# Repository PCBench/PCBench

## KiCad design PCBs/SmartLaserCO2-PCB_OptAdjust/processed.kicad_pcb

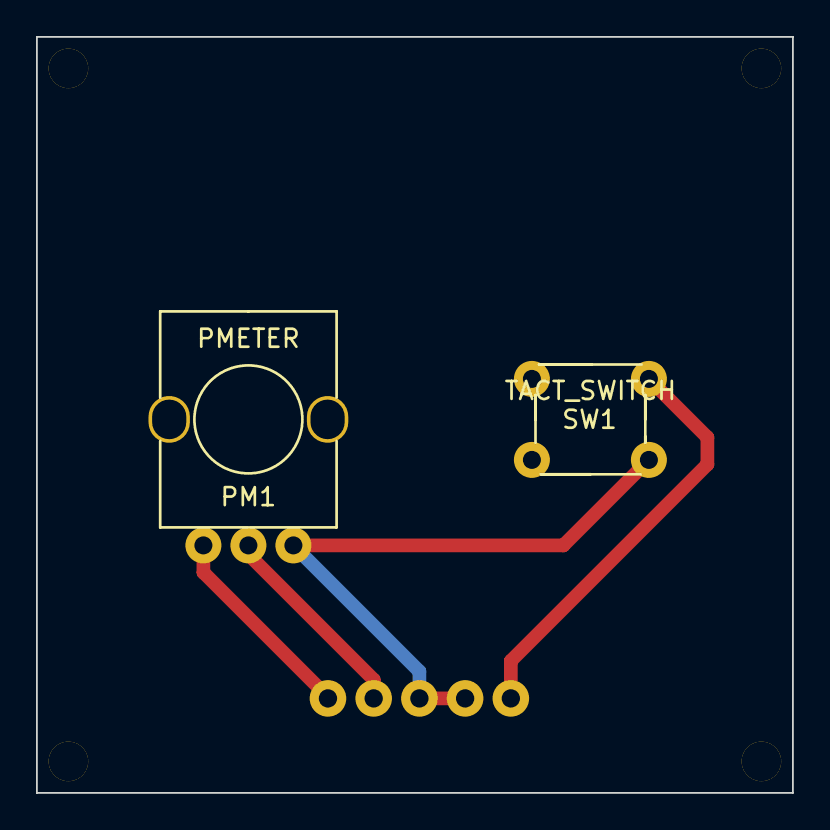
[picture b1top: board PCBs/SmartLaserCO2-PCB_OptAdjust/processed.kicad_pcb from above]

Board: 2 copper layers, 42.0 x 42.0 mm, 7 parts (1 on the bottom side), 4 nets.

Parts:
J1: CONN_5; S5B-XH-A
PM1: PMETER; WH09A-2
Ref**: Val**; HOLE_M2
Ref**_2, Ref**_3, Ref**_4: Val**; HOLE_M2
SW1: TACT_SWITCH; TSA06131

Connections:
GND: J1.3, J1.4, PM1.3, SW1.2
unnamed: J1.1, PM1.1
unnamed: J1.2, PM1.2
unnamed: J1.5, SW1.1

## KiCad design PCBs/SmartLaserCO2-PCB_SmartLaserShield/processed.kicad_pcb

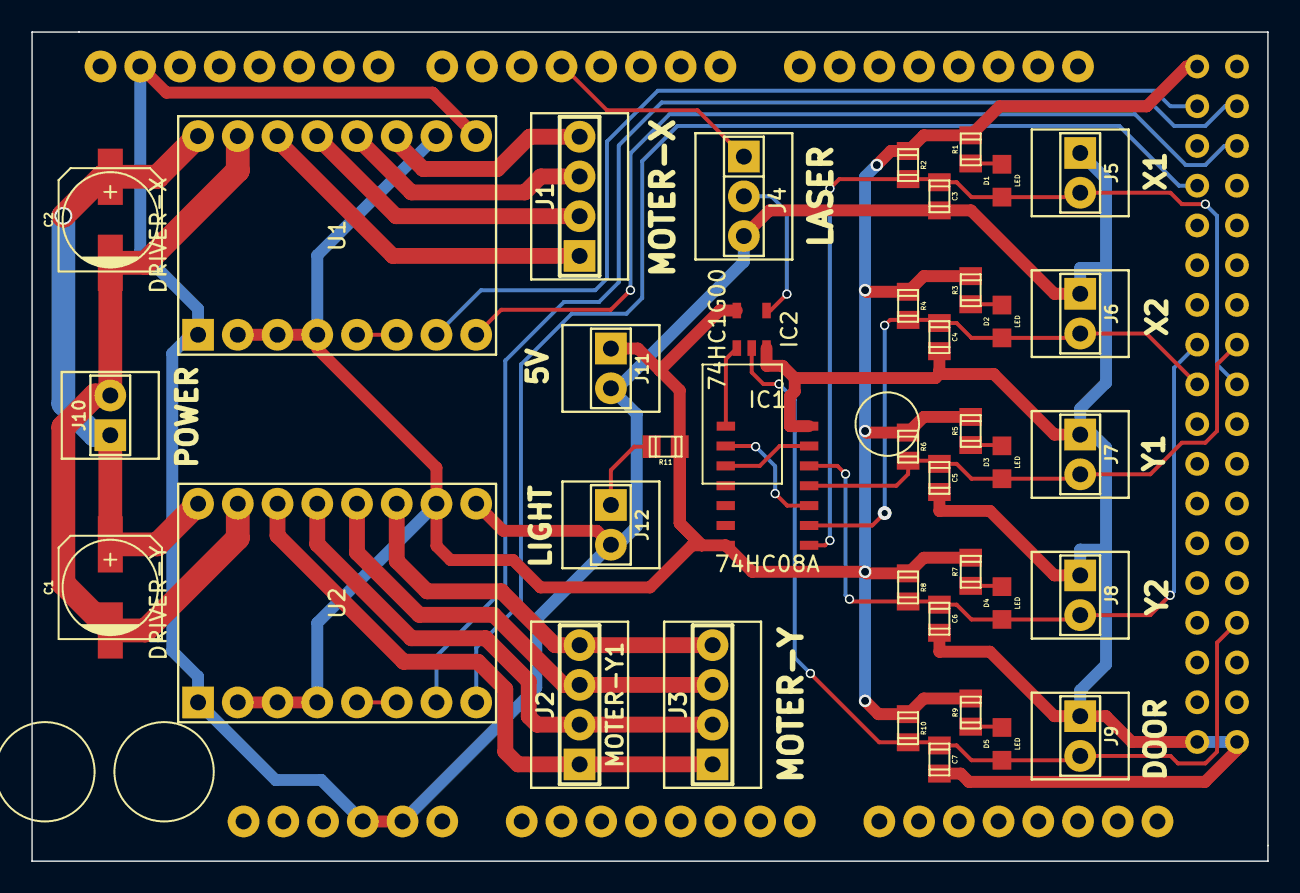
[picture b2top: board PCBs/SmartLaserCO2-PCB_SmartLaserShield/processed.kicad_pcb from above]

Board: 2 copper layers, 79.0 x 53.0 mm, 40 parts (0 on the bottom side), 34 nets.

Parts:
C1, C2: 100uF; C_ELEC_6.3x7.7
C3, C4, C5, C6, C7: 0u1; C_0805
D1, D2, D3, D4, D5: LED; C_LED
IC1: 74HC08A
IC2: 74HC1G00
J1: MOTER-X; PIN_ARRAY_4x1
J2: MOTER-Y1; PIN_ARRAY_4x1
J3: MOTER-Y; PIN_ARRAY_4x1
J4: LASER; PIN_ARRAY_3X1
J5: X1; PIN_ARRAY_2X1
J6: X2; PIN_ARRAY_2X1
J7: Y1; PIN_ARRAY_2X1
J8: Y2; PIN_ARRAY_2X1
J9: DOOR; PIN_ARRAY_2X1
J10: POWER; PIN_ARRAY_2X1
J11: 5V; PIN_ARRAY_2X1
J12: LIGHT; PIN_ARRAY_2X1
R1, R3, R5, R7, R9: 1K; C_0805
R2, R4, R6, R8, R10: 10K; C_0805
R11: 150; C_0805
U1: DRIVER-X; A4988
U2: DRIVER-Y; A4988
U3: ARDUINO_MEGA

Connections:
GND: C3.1, C4.1, C5.1, C6.1, C7.1, IC1.7, IC2.3, J4.3, J5.1, J6.1, J7.1, J8.1, J9.1, J11.2, J12.2, U1.1, U1.9, U2.1, U2.9, U3.GND1, U3.GND2, U3.GND3, U3.GND4, U3.GND5
unnamed: J1.2, U1.13
unnamed: J1.3, U1.12
unnamed: J1.4, U1.11
unnamed: J1.1, U1.14
unnamed: IC1.8, IC2.1
unnamed: J2.3, J3.3, U2.12
unnamed: J2.1, J3.1, U2.14
unnamed: J2.2, J3.2, U2.13
unnamed: J2.4, J3.4, U2.11
unnamed: U1.5, U1.6
unnamed: U2.5, U2.6
unnamed: IC1.3, IC1.9
unnamed: IC1.6, IC1.10
unnamed: J4.1, U3.4
unnamed: U1.7, U3.22
unnamed: U2.7, U3.23
unnamed: IC2.4, J4.2
unnamed: J12.1, R11.1
unnamed: U1.8, U3.25
unnamed: U2.8, U3.26
unnamed: D3.1, R5.2
unnamed: D1.1, R1.2
unnamed: C3.2, D1.2, IC1.1, J5.2, R2.1, U3.37
unnamed: D2.1, R3.2
unnamed: C4.2, D2.2, IC1.2, J6.2, R4.1, U3.36
unnamed: C6.2, D4.2, IC1.5, J8.2, R8.1, U3.34
unnamed: D5.1, R9.2
unnamed: C7.2, D5.2, IC2.2, J9.2, R10.1, U3.49
unnamed: C5.2, D3.2, IC1.4, J7.2, R6.1, U3.35
unnamed: D4.1, R7.2
unnamed: C1.1, C2.1, J10.1, U1.16, U2.16
unnamed: C1.2, C2.2, J10.2, U1.15, U2.15
VDD: IC1.14, IC2.5, J11.1, R1.1, R2.2, R3.1, R4.2, R5.1, R6.2, R7.1, R8.2, R9.1, R10.2, R11.2, U1.2, U1.3, U1.4, U1.10, U2.2, U2.3, U2.4, U2.10, U3.5V_4

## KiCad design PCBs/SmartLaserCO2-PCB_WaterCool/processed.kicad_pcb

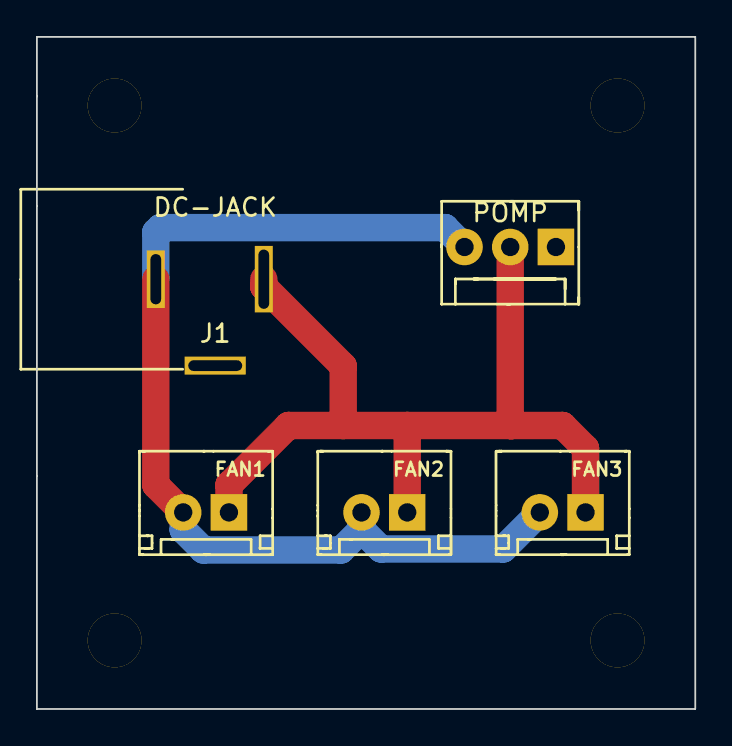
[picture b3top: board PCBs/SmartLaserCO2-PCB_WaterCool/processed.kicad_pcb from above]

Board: 2 copper layers, 36.6 x 37.3 mm, 9 parts (0 on the bottom side), 2 nets.

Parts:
J1: DC-JACK; DC-005
J2: POMP; 640454-3
J3: FAN1; B2B-XH-A
J4: FAN2; B2B-XH-A
J5: FAN3; B2B-XH-A
Ref**: Val**; HOLE_M3
Ref**_2, Ref**_3, Ref**_4: Val**; HOLE_M3

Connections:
+12V: J1.1, J2.2, J3.1, J4.1, J5.1
GND: J1.2, J2.3, J3.2, J4.2, J5.2

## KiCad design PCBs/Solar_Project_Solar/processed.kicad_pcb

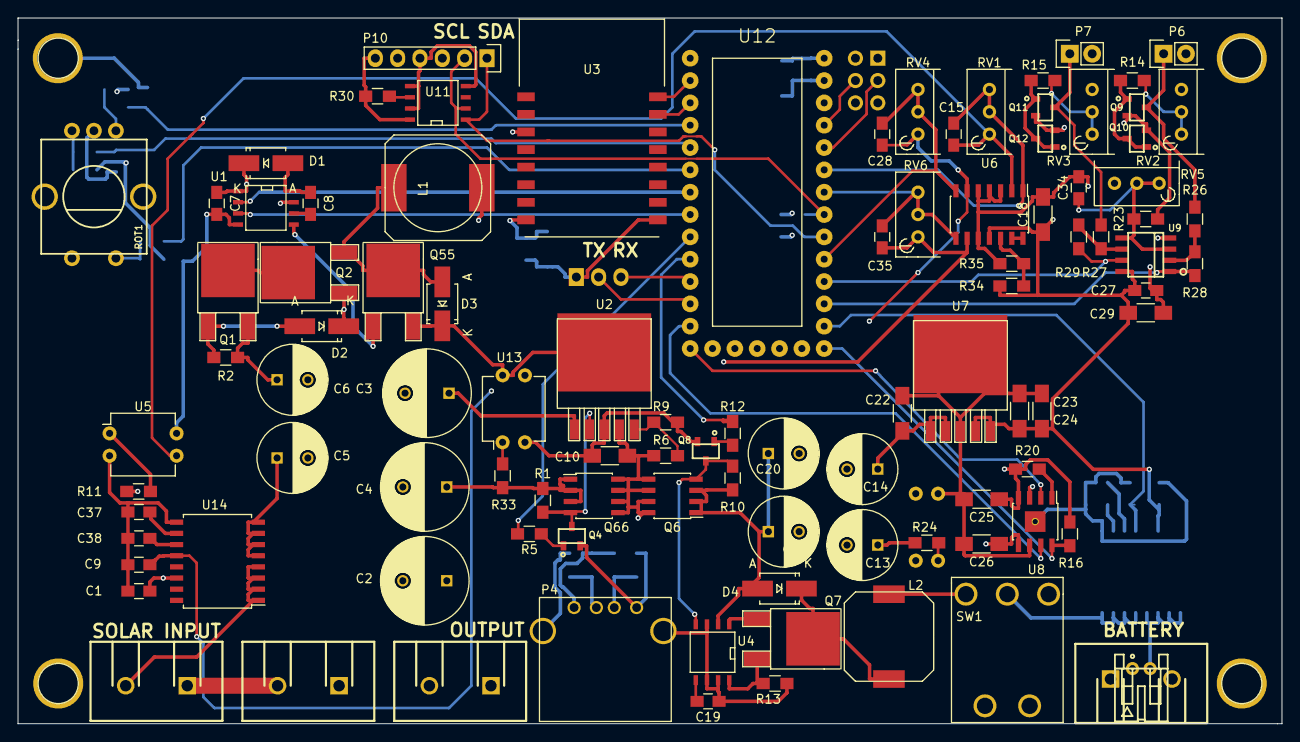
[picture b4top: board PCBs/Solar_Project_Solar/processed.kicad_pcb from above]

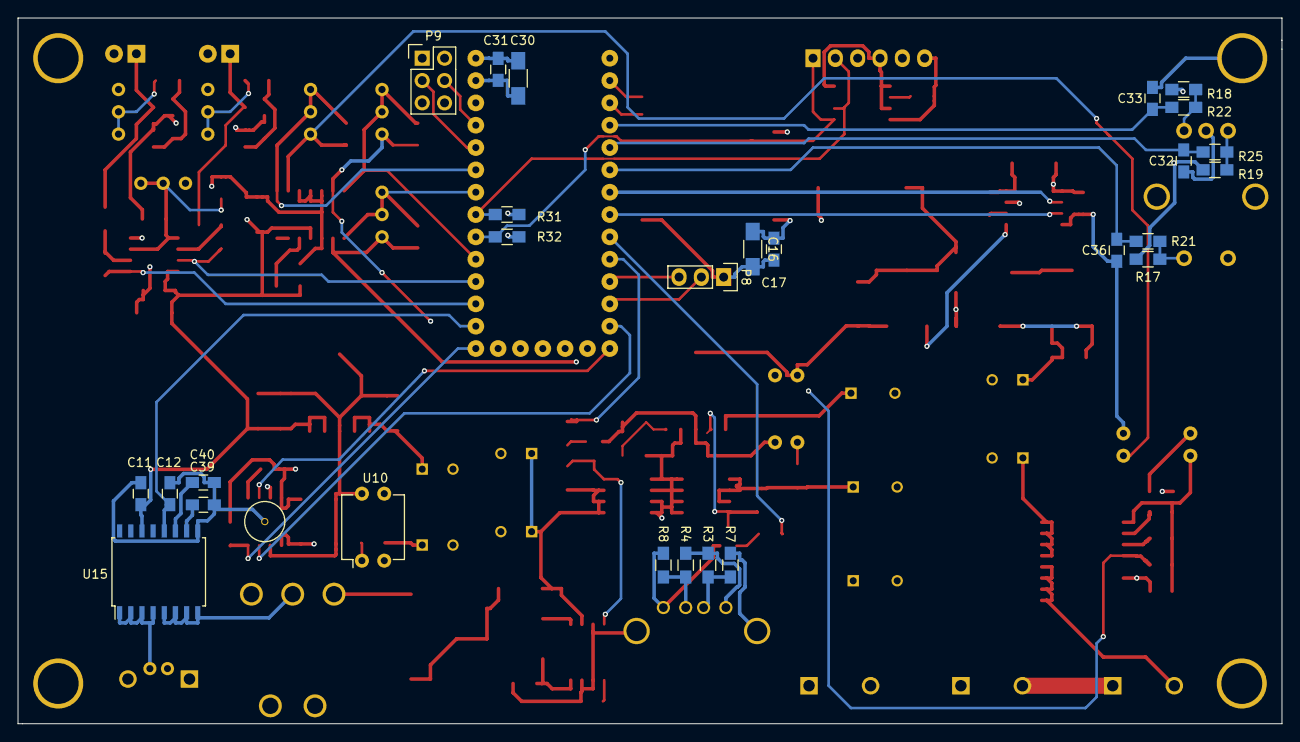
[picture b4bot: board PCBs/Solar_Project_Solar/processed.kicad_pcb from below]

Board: 4 copper layers, 143.8 x 80.3 mm, 127 parts (27 on the bottom side), 80 nets.

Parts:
C1, C7, C8, C9, C11, C12, C17, C19, C27, C31, C37, C38, C39, C40: .1u; C_0805_HandSoldering
C2, C3, C4: 1000u; C_Radial_D10_L16_P5
C5, C6, C13, C14, C20, C21: 220U; C_Radial_D8_L11.5_P3.5
C10, C16, C18, C22, C23, C24, C25, C26, C29, C30: 22U; C_1206_HandSoldering
C15, C28, C32, C33, C35, C36: .01u; C_0805_HandSoldering
C34: 1u; C_0805_HandSoldering
D1, D2, D3, D4: MBRA340T3G; Diode-SMA_Handsoldering
JST-S2B-PH-K_right-angle-jack: VAL**; JST-S2B-PH-K_right-angle-jack
L1: 330uH; SELF-WE-PD-XXL
L2: 22U; self_cms_we-tpc_XL
P1, P2, P3, P5: CONN_01X02; 1x2-SCREW-TERM_P7.5mm
P4: USB_A
P6, P7: CONN_01X02; Pin_Header_Straight_1x02
P8: CONN_01X03; Pin_Header_Straight_1x03
P9: CONN_02X03; Pin_Header_Straight_2x03
P10: CONN_01X06; Pin_Header_Straight_1x06
Q1, Q2, Q7, Q55: IRF3704Z; DPAK-2
Q4, Q8: PN2222A; SOT23
Q6, Q66: FDS4465; SOIC-8_3.9x4.9mm_Pitch1.27mm
Q9, Q10, Q11, Q12: PNP_BEC; SOT23
R1, R10: 330k; R_0805_HandSoldering
R2, R11, R16, R17, R18, R19, R20, R21, R22, R25, R30, R34, R35: 10k; R_0805_HandSoldering
R3: 42.9k; R_0805_HandSoldering
R4: 74.4k; R_0805_HandSoldering
R5, R12: 1k; R_0805_HandSoldering
R6: 180k; R_0805_HandSoldering
R7, R8: 49.3k; R_0805_HandSoldering
R9: 16k; R_0805_HandSoldering
R13: 50m; R_0805_HandSoldering
R14, R15: 2.2k; R_0805_HandSoldering
R23, R24: 2.7k; R_0805_HandSoldering
R26, R27: 12k; R_0805_HandSoldering
R28, R29: 47k; R_0805_HandSoldering
R31, R32: 4.7k; R_0805_HandSoldering
R33: 3.3k; R_0805_HandSoldering
ROT1: ROTARY-ENCODER; SF-ROTARY-ENCODER
RV1, RV4, RV6: POT; Potentiometer_Bourns_3296W_3-8Zoll_Inline_ScrewUp
RV2, RV3, RV5: 1k; Potentiometer_Bourns_3296W_3-8Zoll_Inline_ScrewUp
SW1: SW_SPDT; SPDT_Toggle
U1: IR2104; SOIC-8-N
U2: MCP1827; DPAK-5
U3: ESP8266; ESP8266_ADAFRUIT_SMD
U4: MAX770; SOIC-8-N
U5, U10, U13: LTV-817; DIP-4_W7.62mm
U6: LMV324; SOIC-14_3.9x8.7mm_Pitch1.27mm
U7: LT1963; DPAK-5
U8: MAX1811; SOIC-8-1EP_3.9x4.9mm_Pitch1.27mm
U9: TL072; SOIC8
U11: DS75; SOIC-8-N
U12: Teensy_3.1
U14, U15: ACS710; SOIC-16_7.5x10.3mm_Pitch1.27mm

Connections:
5V_OUT: C10.1, C25.1, P1.1, P4.1, P9.1, P9.2, Q6.5, Q6.6, Q6.7, Q6.8, Q66.5, Q66.6, Q66.7, Q66.8, R3.1, R4.1, R6.1, R16.1, R20.1, U2.4, U8.4
+3V3: C1.1, C11.1, C16.1, C17.1, C18.1, C23.1, C24.1, C27.1, C29.1, C30.1, C31.1, P10.6, Q9.2, Q10.2, Q11.2, Q12.2, R17.1, R18.1, R19.1, R23.1, R30.1, R31.1, R32.1, R34.1, U3.3, U3.8, U6.11, U7.4, U7.5, U9.8, U11.8, U12.26, U14.14, U15.14
BATTERY_I: C12.1, U12.14, U15.12
BATTERY_INPUT: C13.1, C14.1, C22.1, L2.1, R24.1, SW1.2, U7.1, U7.2
BATTERY_INPUT_BUF: C28.2, RV4.2, RV4.3, U6.7, U12.17
CHRG: R16.2, U8.8, U12.13
CHRG_EN: U8.7, U12.11
CHRG_I: U8.2, U12.12
ESP_RX: U3.15, U12.1
ESP_TX: U3.16, U12.0
GND: C1.2, C2.2, C3.2, C4.2, C5.2, C6.2, C7.2, C9.2, C10.2, C11.2, C12.2, C13.2, C14.2, C16.2, C17.2, C18.2, C19.2, C20.2, C21.2, C22.2, C23.2, C24.2, C25.2, C26.2, C27.2, C29.2, C30.2, C31.2, C32.2, C33.2, C34.2, C36.2, C37.2, C38.2, C39.2, C40.2, D3.1, JST-S2B-PH-K_right-angle-jack.1, P1.2, P3.1, P4.4, P4.5, P5.1, P6.2, P7.2, P8.1, P9.5, P9.6, P10.4, Q4.2, Q8.2, Q55.3, R7.2, R8.2, R9.2, R13.2, R35.2, ROT1.3, ROT1.5, RV2.3, RV3.3, RV5.3, U1.4, U2.3, U3.9, U4.3, U4.6, U4.7, U5.2, U5.4, U6.3, U6.4, U6.5, U6.10, U7.3, U8.3, U8.6, U9.4, U10.2, U10.4, U11.4, U11.5, U11.7, U12.25, U12.27, U12.30, U13.2, U13.4, U14.9, U15.9
LIGHT1: R28.2, U9.1, U12.15
LIGHT2: R29.1, U9.7, U12.16
LOAD_SWITCH: R12.1, U12.8
MPPT_PWM: U1.2, U12.5
unnamed: C5.1, C6.1, C7.1, D1.1, Q1.3, R2.1, U1.1, U14.5, U14.6, U14.7, U14.8
unnamed: C8.1, D1.2, U1.8
unnamed: C8.2, U1.6
unnamed: C15.1, RV1.1, U5.3, U6.2
unnamed: C19.1, U4.5
unnamed: C20.1, C21.1, D4.2, Q6.1, Q6.2, Q6.3, R10.2, U4.2
unnamed: C26.1, SW1.1, U8.5, U15.5, U15.6, U15.7, U15.8
unnamed: C28.1, RV4.1, U6.6, U10.3
unnamed: C34.1, R23.2, RV5.1, RV5.2, U9.3, U9.5
unnamed: C35.1, RV6.1, U6.9, U13.3
unnamed: C37.1, U14.10
unnamed: C38.1, U14.11
unnamed: C39.1, U15.10
unnamed: C40.1, U15.11
unnamed: D2.1, Q2.1, U1.7
unnamed: D2.2, Q1.1, R2.2
unnamed: D3.2, L1.1, Q2.3, Q55.2
unnamed: D4.1, L2.2, Q7.2
unnamed: P2.1, P3.2
unnamed: P4.2, R3.2, R7.1
unnamed: P4.3, R4.2, R8.1
unnamed: JST-S2B-PH-K_right-angle-jack.2, P5.2, U15.1, U15.2, U15.3, U15.4
unnamed: P6.1, Q10.3, R26.1
unnamed: P7.1, Q11.3, R27.1
unnamed: Q1.2, Q2.2
unnamed: Q4.1, R5.1
unnamed: Q4.3, Q66.4, R1.2, U2.2
unnamed: Q6.4, Q8.3, R10.1, U4.4
unnamed: Q7.1, U4.1
unnamed: Q7.3, R13.1, U4.8
unnamed: Q8.1, R12.2
unnamed: Q9.1, Q9.3, Q10.1, R14.1
unnamed: Q11.1, Q12.1, Q12.3, R15.1
unnamed: Q55.1, U1.5
unnamed: R6.2, R9.1, U2.5
unnamed: R11.2, U5.1
unnamed: R14.2, RV2.1, RV2.2
unnamed: R15.2, RV3.1, RV3.2
unnamed: R17.2, R21.2, ROT1.1
unnamed: R18.2, R22.2, ROT1.2
unnamed: R19.2, R25.2, ROT1.4
unnamed: R20.2, U8.1
unnamed: R24.2, U10.1
unnamed: R26.2, R28.1, U9.2
unnamed: R27.2, R29.2, U9.6
unnamed: R30.2, U11.6
unnamed: R33.2, U13.1
unnamed: R34.2, R35.1, U6.12
unnamed: U6.13, U6.14
PRE_REG_V: C2.1, C3.1, C4.1, L1.2, Q66.1, Q66.2, Q66.3, R1.1, R33.1, U2.1
PRE_REG_V_BUF: C35.2, RV6.2, RV6.3, U6.8, U12.20
REGULATE: R5.2, U12.7
ROTARY_A: C33.1, R22.1, U12.2
ROTARY_B: C32.1, R25.1, U12.3
ROTARY_BUTTON: C36.1, R21.1, U12.4
RXD: P8.2, U12.10
SCL: P10.2, R31.2, U11.2, U12.19
SDA: P10.1, R32.2, U11.1, U12.18
SERVO1: P9.3, U12.22
SERVO2: P9.4, U12.23
SOLAR_I: C9.1, U12.28, U14.12
SOLAR_INPUT: P2.2, R11.1, U14.1, U14.2, U14.3, U14.4
SOLAR_INPUT_BUF: C15.2, RV1.2, RV1.3, U6.1, U12.21
SOLAR_SHDN: U1.3, U12.6
TXD: P8.3, U12.9

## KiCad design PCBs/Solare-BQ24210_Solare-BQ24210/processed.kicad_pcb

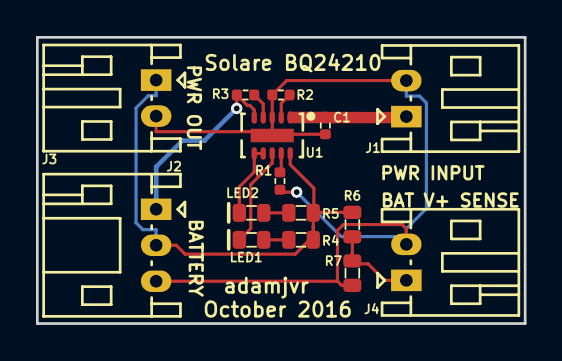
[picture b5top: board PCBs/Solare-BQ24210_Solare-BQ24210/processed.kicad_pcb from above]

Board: 2 copper layers, 27.1 x 15.9 mm, 15 parts (0 on the bottom side), 12 nets.

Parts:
C1: CL05A105KA5NQNC; C0402
J1, J3, J4: S2B-PH-K-S(LF)(SN)
J2: S3B-PH-K-S(LF)(SN)
LED1: LTST-C191KGKT; LED0603
LED2: LTST-C191KFKT; LED0603
R1, R3: RC1005F102CS; R0402
R2: RC1005F4870CS; R0402
R4, R5: RC1608J202CS; R0603
R6, R7: ERA-3AEB3741V; R0603
U1: BQ24210DQCT; BQ24210

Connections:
/BAT: J2.2, J3.1, R4.2, R5.2, R6.1, U1.10
/BAT_VOLT: J4.1, R6.2, R7.1
/THERM: J2.1, R3.2, U1.5
GND: C1.2, J1.2, J2.3, J3.2, J4.2, R1.2, R2.2, R7.2, U1.3, U1.11
unnamed: C1.1, J1.1, U1.1
unnamed: LED1.1, R4.1
unnamed: LED1.2, U1.8
unnamed: LED2.1, R5.1
unnamed: LED2.2, U1.6, U1.7
unnamed: R1.1, U1.9
unnamed: R2.1, U1.2
unnamed: R3.1, U1.4

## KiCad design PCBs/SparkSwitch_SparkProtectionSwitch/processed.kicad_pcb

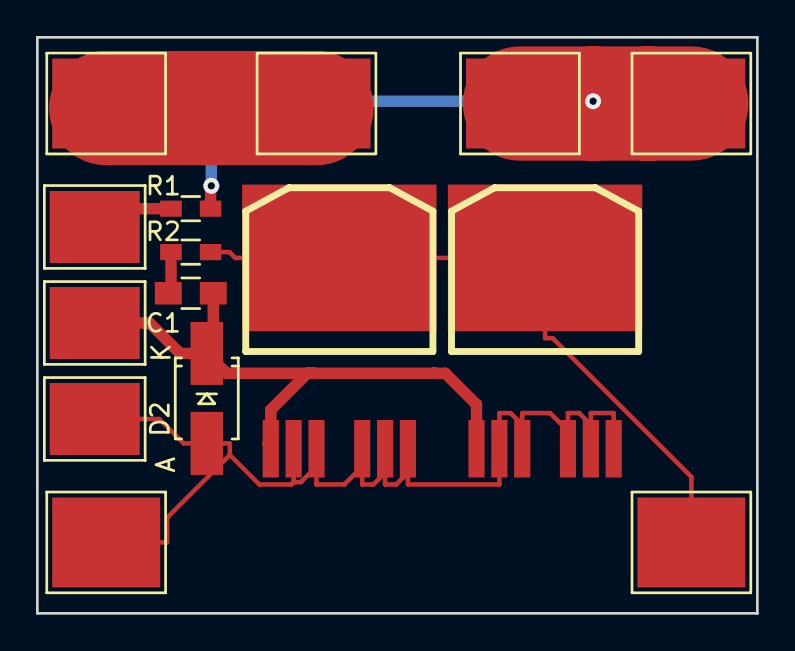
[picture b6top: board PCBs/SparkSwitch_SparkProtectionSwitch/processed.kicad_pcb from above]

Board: 2 copper layers, 40.0 x 32.0 mm, 15 parts (0 on the bottom side), 7 nets.

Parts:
C1: 1u/100V; C_0805_HandSoldering
D2: ZENERsmall; Diode-SMA_Handsoldering
P1: IN+; 1PAD_6x5mm
P2: IN-; 1PAD_6x5mm
P3: SW; 1PAD_4x5mm
P4: OUT+; 1PAD_6x5mm
P5: OUT-; 1PAD_6x5mm
P6: FUSE_A; 1PAD_6x5mm
P7, P8: 12V_SW; 1PAD_4x5mm
P9: FUSE_B; 1PAD_6x5mm
Q1, Q2: IRFS7530; D2PAK-7-GDS
R1: 1M; R_0603_HandSoldering
R2: 1k; R_0603_HandSoldering

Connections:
unnamed: C1.1, R2.2
unnamed: C1.2, D2.2, P7.1, Q1.G, Q2.G
unnamed: D2.1, P2.1, P8.1, Q1.S, Q2.S
unnamed: P1.1, P6.1
unnamed: P3.1, R1.2
unnamed: P4.1, P9.1, R1.1
unnamed: P5.1, Q1.D, Q2.D, R2.1

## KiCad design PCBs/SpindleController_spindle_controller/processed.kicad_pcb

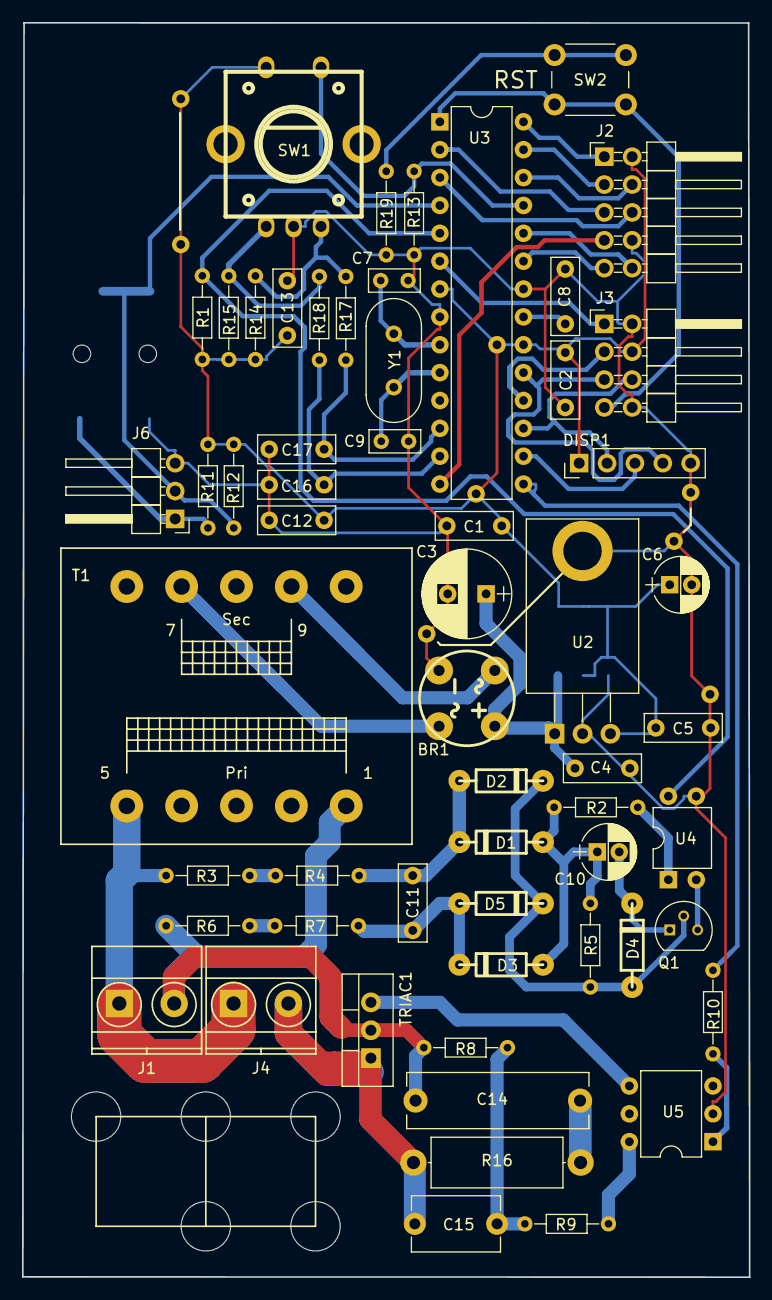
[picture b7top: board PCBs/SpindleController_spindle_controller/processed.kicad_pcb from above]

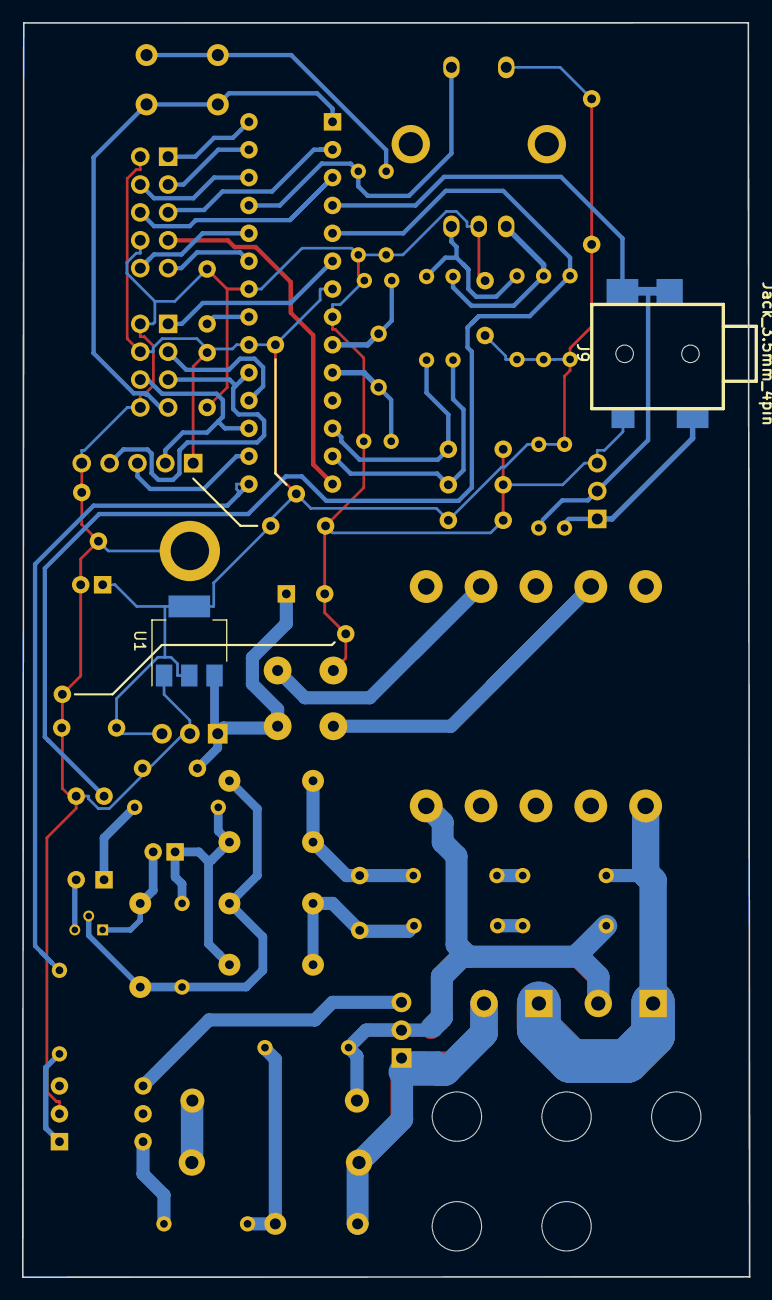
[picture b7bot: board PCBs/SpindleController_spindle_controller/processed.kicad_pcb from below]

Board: 2 copper layers, 66.3 x 114.4 mm, 69 parts (2 on the bottom side), 49 nets.

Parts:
BR1: D_Bridge_+AA-; bridge_wob
C1, C2, C5, C8, C12, C13: 100n; C_Rect_L7.0mm_W2.5mm_P5.00mm
C3: 220u; CP_Radial_D8.0mm_P3.50mm
C4: 470n; C_Rect_L7.0mm_W2.5mm_P5.00mm
C6: 100u; CP_Radial_D5.0mm_P2.00mm
C7, C9: 27p; C_Rect_L4.6mm_W2.0mm_P2.50mm_MKS02_FKP02
C10: 10u; CP_Radial_D5.0mm_P2.00mm
C11: 1n; C_Rect_L7.0mm_W2.5mm_P5.00mm
C14: 10n; C_Rect_L16.5mm_W5.0mm_P15.00mm_MKT
C15: 1n; C_Disc_D8.0mm_W5.0mm_P7.50mm
C16, C17: 47n; C_Rect_L7.0mm_W2.5mm_P5.00mm
D1, D2, D3, D4, D5: 1N4841; diode_do35
DISP1: 8x7SEG; Pin_Header_Straight_1x05_Pitch2.54mm
J1: VAC 230V; TerminalBlock_Pheonix_MKDS1.5-2pol
J2: AUX/CONTROL; Pin_Header_Angled_2x05_Pitch2.54mm
J3: ICP; Pin_Header_Angled_2x04_Pitch2.54mm
J4: Load output; TerminalBlock_Pheonix_MKDS1.5-2pol
J6: CONN_01X03; Pin_Header_Angled_1x03_Pitch2.54mm
J7, J7_2, J7_3, J7_4: GND_JUMPER; JUMPER_PIN
J8, J8_2, J8_3, J8_4: VCC_JUMPER; JUMPER_PIN
J9: Jack_3.5mm_4pin; jack_3.5_sj1-3514-smt
Q1: 2N3904; TO-92_Molded_Narrow
R1, R12, R13, R14, R15: 10k; R_Axial_DIN0204_L3.6mm_D1.6mm_P7.62mm_Horizontal
R2, R10: 1k; R_Axial_DIN0204_L3.6mm_D1.6mm_P7.62mm_Horizontal
R3, R6: 120k; R_Axial_DIN0204_L3.6mm_D1.6mm_P7.62mm_Horizontal
R4, R7: 220k; R_Axial_DIN0204_L3.6mm_D1.6mm_P7.62mm_Horizontal
R5: 33k; R_Axial_DIN0204_L3.6mm_D1.6mm_P7.62mm_Horizontal
R8: 470; R_Axial_DIN0204_L3.6mm_D1.6mm_P7.62mm_Horizontal
R9, R19: 360; R_Axial_DIN0204_L3.6mm_D1.6mm_P7.62mm_Horizontal
R11: 220; R_Axial_DIN0204_L3.6mm_D1.6mm_P7.62mm_Horizontal
R16: 47; R_Axial_DIN0414_L11.9mm_D4.5mm_P15.24mm_Horizontal
R17, R18: 2k2; R_Axial_DIN0204_L3.6mm_D1.6mm_P7.62mm_Horizontal
SW1: Rotary_Encoder_Switch; encoder_alps-ec12d
SW2: SW_SPST; SW_PUSH_6mm
T1: 230 - 6VAC (Spitznagel SPK 01406); Trafo_CHK-EI30-2VA_1xSec
TRIAC1: BT138; TO-220_Vertical
U1: LT1117-5; SOT-223
U2: LM2940CT-5.0; TO-220_Horizontal_connected_tab
U3: ATMEGA328P-PU; DIP-28_W7.62mm
U4: PC817; DIP-4_W7.62mm
U5: MOC3020M; DIP-6_W7.62mm
WIRESTRAP1: 2x Ziplock wire strap; WireStrap_2X_5HOLES
Y1: 16MHz; Crystal_HC49-U_Vertical

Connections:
/DBG: J3.1, U3.6
/MISO: J3.3, U3.18
/MOSI: DISP1.2, J3.6, U3.17
/PB0: J2.7, U3.14
/PC3: J2.4, U3.26
/PD6: J2.9, U3.23
/PD7: J2.10, U3.24
/RENC_A: C16.2, R18.2, U3.13
/RENC_B: C17.2, R17.2, U3.12
/ROT_PULSE: J6.2, J9.2, J9.3, R12.1, U3.4
/RST: J3.7, SW2.1, U3.1
/RX: J2.5, U3.2
/SCK: DISP1.4, J3.5, U3.19
/SCL: J2.1, U3.28
/SDA: J2.3, U3.27
/SEG_CS: DISP1.3, U3.16
/SW1: R13.2, SW1.4, U3.25
/TRIAC_DRIVE: R10.1, U3.15
/TX: J2.6, U3.3
/VAC_L: C14.1, J1.2, R6.2, R8.2, T1.1, TRIAC1.2
/VAC_N: J1.1, J4.1, R3.2, T1.5
/ZCROSS_PULSE: R1.1, U3.5, U4.4
GND: BR1.4, C1.2, C2.1, C3.2, C4.2, C5.2, C6.2, C7.2, C8.2, C9.2, C12.2, C13.1, C16.1, C17.1, DISP1.5, J2.8, J3.2, J3.8, J6.3, J7.1, J7_2.1, J7_3.1, J7_4.1, J9.4, R13.1, R19.2, SW1.2, U1.1, U2.2, U3.8, U3.22, U4.3, U5.2
unnamed: BR1.1, C3.1, C4.1, U1.3, U2.1
unnamed: BR1.2, T1.9
unnamed: BR1.3, T1.7
unnamed: C7.1, U3.9, Y1.1
unnamed: C8.1, U3.21
unnamed: C9.1, U3.10, Y1.2
unnamed: C10.1, D1.1, D3.1, R2.2, R5.2
unnamed: C10.2, D4.2, Q1.1
unnamed: C11.1, D1.2, D2.1, R4.1
unnamed: C11.2, D3.2, D5.1, R7.1
unnamed: C14.2, R16.2
unnamed: C15.1, R8.1, R9.2
unnamed: C15.2, J4.2, R16.1, TRIAC1.1
unnamed: D2.2, D4.1, D5.2, Q1.2, R5.1
unnamed: J6.1, J9.1, R11.2
unnamed: Q1.3, U4.2
unnamed: R2.1, U4.1
unnamed: R3.1, R4.2
unnamed: R6.1, R7.2
unnamed: R9.1, U5.6
unnamed: R10.2, U5.1
unnamed: R14.1, R17.1, SW1.3
unnamed: R15.1, R18.1, SW1.1
unnamed: R19.1, SW2.2
unnamed: TRIAC1.3, U5.4
VCC: C1.1, C2.2, C5.1, C6.1, C12.1, C13.2, DISP1.1, J2.2, J3.4, J8.1, J8_2.1, J8_3.1, J8_4.1, R1.2, R11.1, R12.2, R14.2, R15.2, SW1.5, U1.2, U1.4, U2.3, U3.7, U3.20
